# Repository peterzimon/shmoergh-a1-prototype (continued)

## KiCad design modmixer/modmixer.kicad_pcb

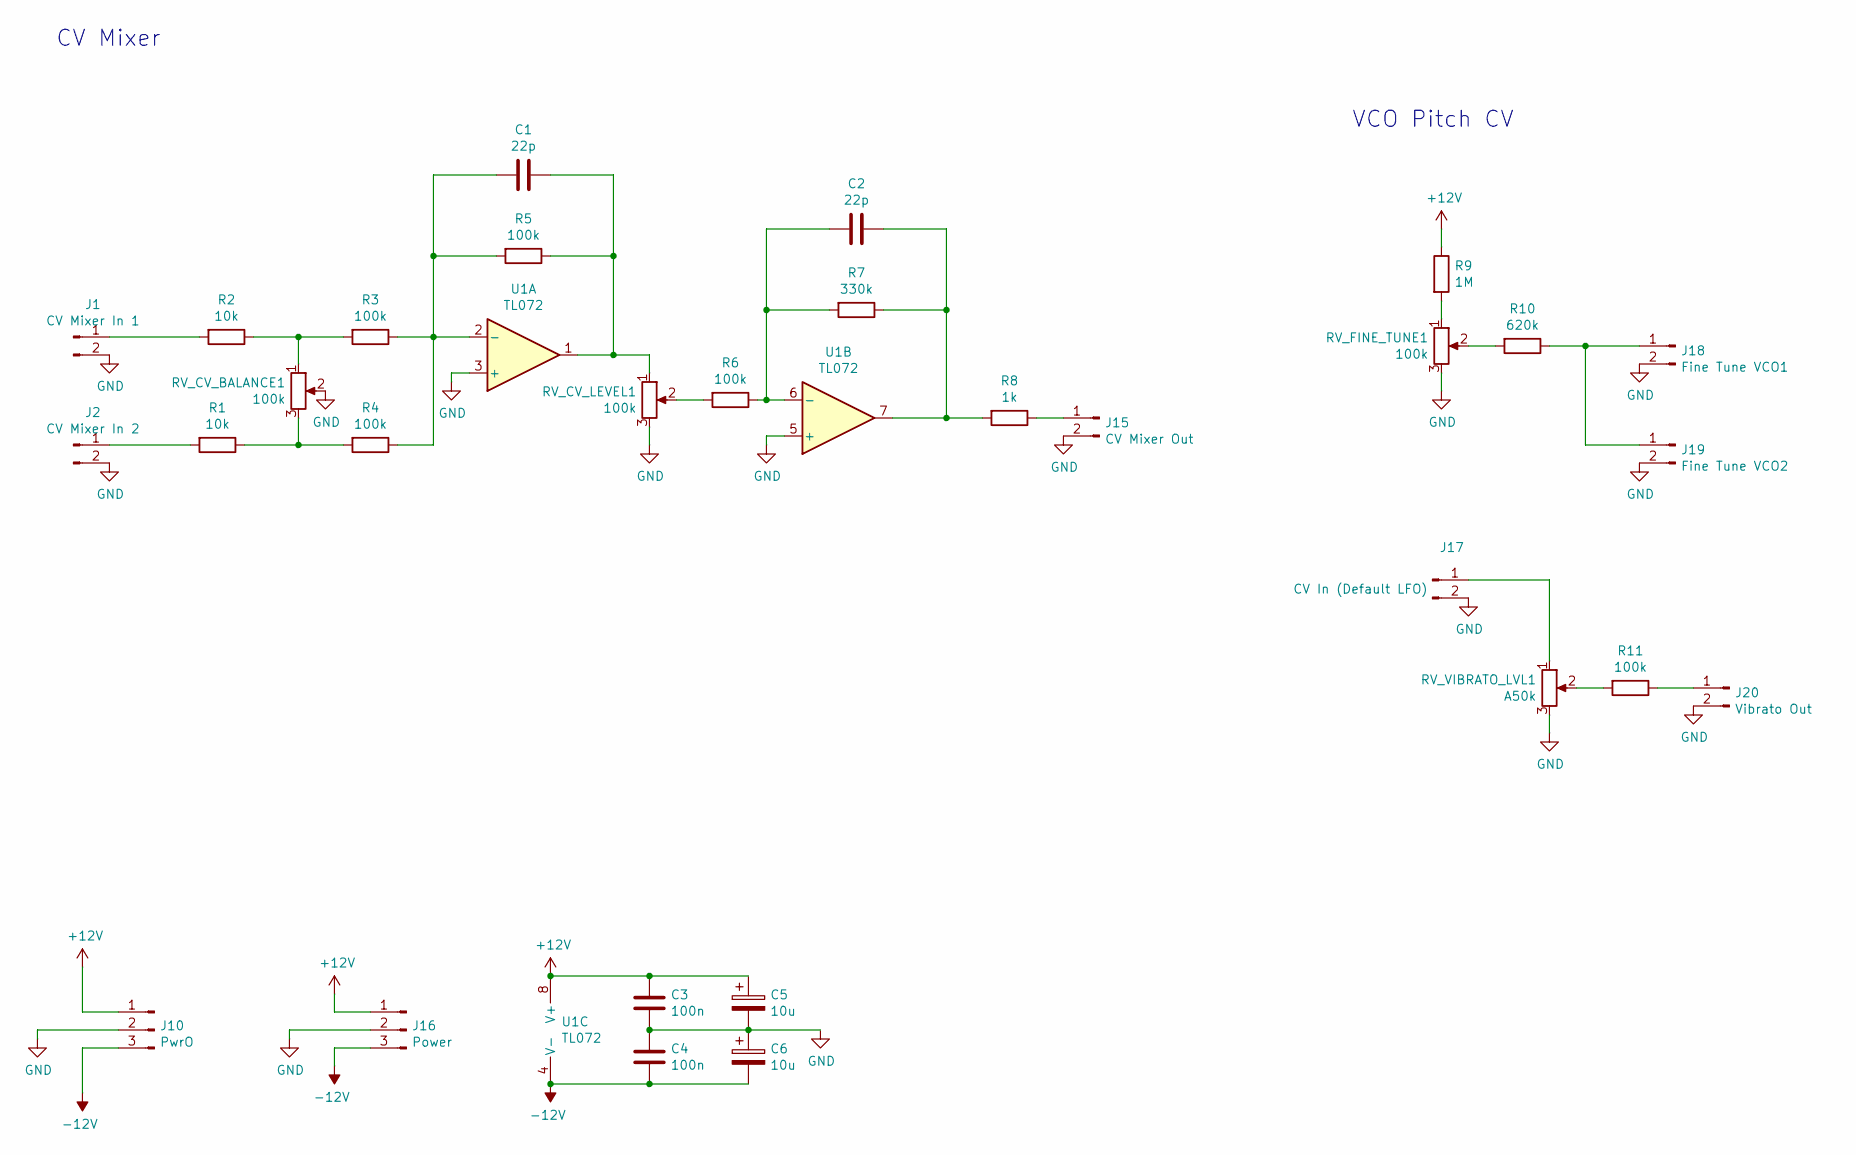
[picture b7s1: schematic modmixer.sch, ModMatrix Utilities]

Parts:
C1, C2: 22p; C_Disc_D5.0mm_W2.5mm_P2.50mm
C3, C4: 100n; C_Disc_D5.0mm_W2.5mm_P2.50mm
C5, C6: 10u; CP_Radial_D5.0mm_P2.50mm
J1: CV Mixer In 1; NSL25_01x02_Vertical
J2: CV Mixer In 2; NSL25_01x02_Vertical
J10: PwrO; NSL25_01x03_Vertical
J15: CV Mixer Out; NSL25_01x02_Vertical
J16: Power; NSL25_01x03_Vertical
J17: CV In (Default LFO); NSL25_01x02_Vertical
J18: Fine Tune VCO1; NSL25_01x02_Vertical
J19: Fine Tune VCO2; NSL25_01x02_Vertical
J20: Vibrato Out; NSL25_01x02_Vertical
R1, R2: 10k; R_Axial_Vertical
R3, R4, R5, R6, R11: 100k; R_Axial_Vertical
R7: 330k; R_Axial_Vertical
R8: 1k; R_Axial_Vertical
R9: 1M; R_Axial_Vertical
R10: 620k; R_Axial_Vertical
RV_CV_BALANCE1: 100k; NSL25_01x03_Vertical
RV_CV_LEVEL1: 100k; NSL25_01x03_Vertical
RV_FINE_TUNE1: 100k; NSL25_01x03_Vertical
RV_VIBRATO_LVL1: A50k; NSL25_01x03_Vertical
U1: TL072; DIP-8_W7.62mm

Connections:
+12V: C3.1, C5.1, J10.1, J16.1, R9.1, U1.8 (V+)
-12V: C4.2, C6.2, J10.3, J16.3, U1.4 (V-)
GND: C3.2, C4.1, C5.2, C6.1, J1.2, J2.2, J10.2, J15.2, J16.2, J17.2, J18.2, J19.2, J20.2, RV_CV_BALANCE1.2, RV_CV_LEVEL1.3, RV_FINE_TUNE1.3, RV_VIBRATO_LVL1.3, U1.3 (+), U1.5 (+)
unnamed: C1.1, R5.1, RV_CV_LEVEL1.1, U1.1
unnamed: C1.2, R3.1, R4.1, R5.2, U1.2 (-)
unnamed: C2.1, R7.1, R8.2, U1.7
unnamed: C2.2, R6.1, R7.2, U1.6 (-)
unnamed: J1.1, R2.2
unnamed: J2.1, R1.2
unnamed: J15.1, R8.1
unnamed: J17.1, RV_VIBRATO_LVL1.1
unnamed: J18.1, J19.1, R10.1
unnamed: J20.1, R11.1
unnamed: R1.1, R4.2, RV_CV_BALANCE1.3
unnamed: R2.1, R3.2, RV_CV_BALANCE1.1
unnamed: R6.2, RV_CV_LEVEL1.2
unnamed: R9.2, RV_FINE_TUNE1.1
unnamed: R10.2, RV_FINE_TUNE1.2
unnamed: R11.2, RV_VIBRATO_LVL1.2

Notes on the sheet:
CV Mixer
VCO Pitch CV

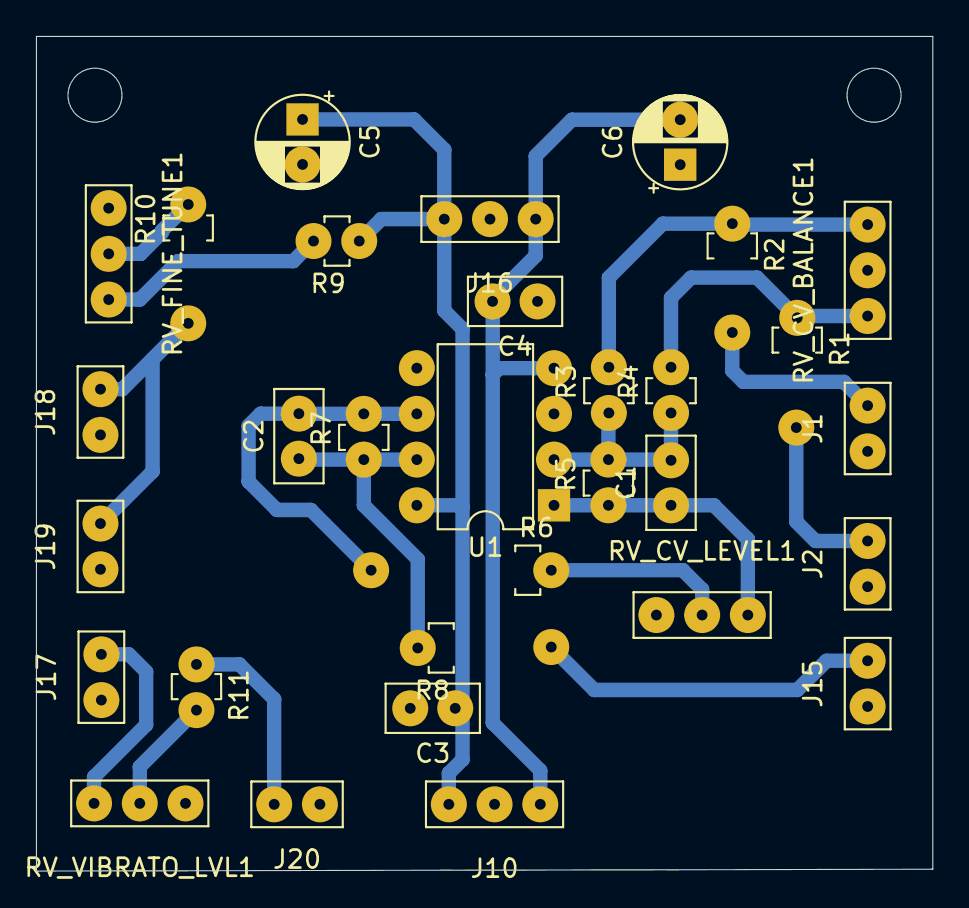
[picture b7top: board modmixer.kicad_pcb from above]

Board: 2 copper layers, 49.8 x 46.4 mm, 31 parts (0 on the bottom side), 19 nets.

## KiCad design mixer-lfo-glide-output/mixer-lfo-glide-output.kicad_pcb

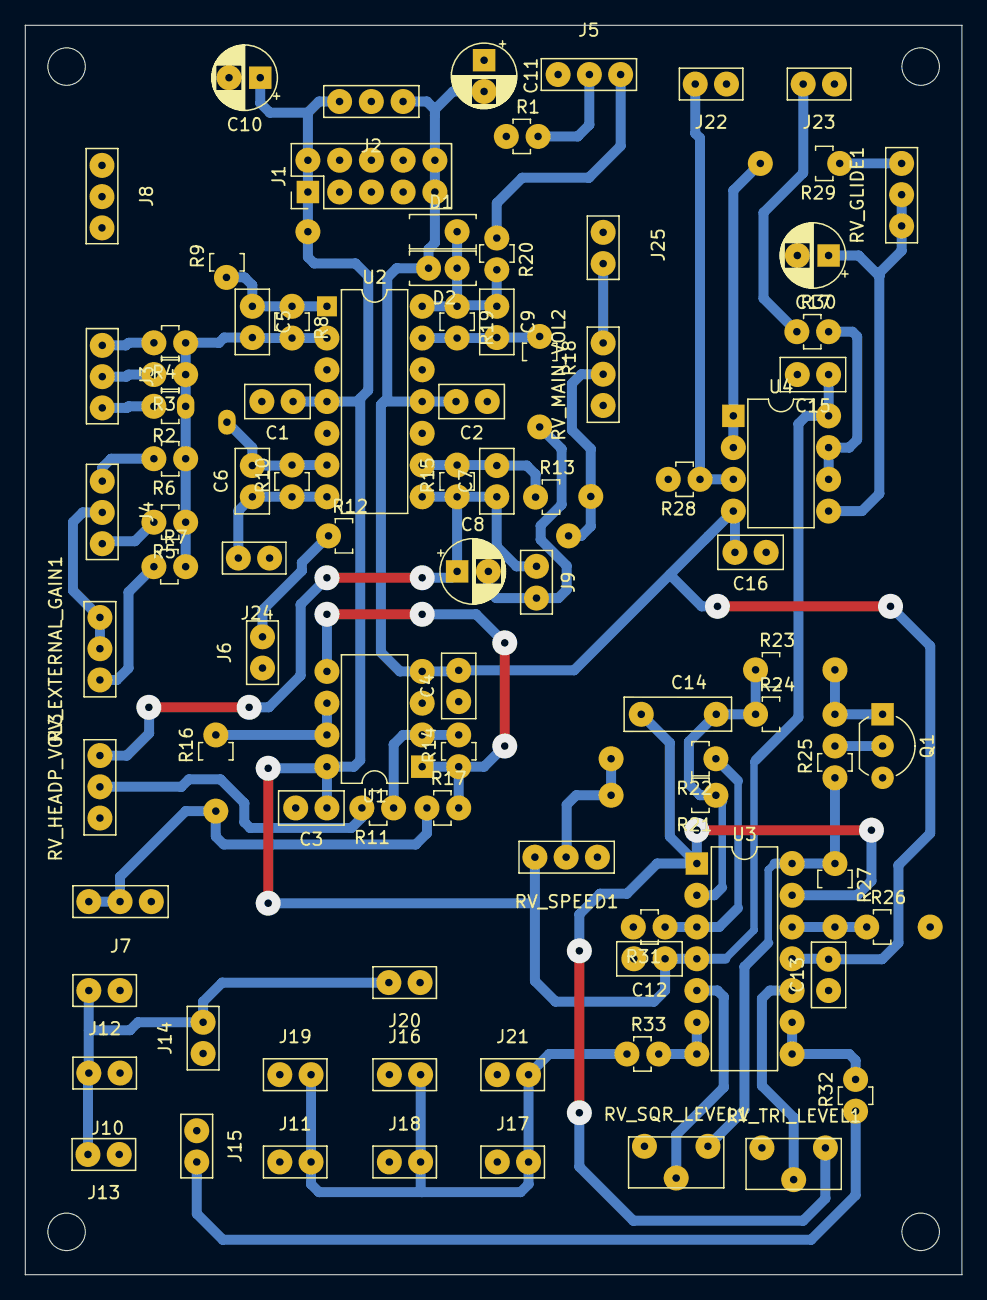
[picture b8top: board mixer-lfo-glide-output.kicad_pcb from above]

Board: 2 copper layers, 74.9 x 99.9 mm, 89 parts (0 on the bottom side), 50 nets.

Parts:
C1, C2, C3, C4, C12, C13, C15, C16: 100n; C_Disc_D5.0mm_W2.5mm_P2.50mm
C5, C6: 47p; C_Disc_D5.0mm_W2.5mm_P2.50mm
C7, C9: 22p; C_Disc_D5.0mm_W2.5mm_P2.50mm
C8, C10, C11: 10u; CP_Radial_D5.0mm_P2.50mm
C14: 100n; C_Foil_P2.50mm
C17: 1u; CP_Radial_D5.0mm_P2.50mm
D1, D2: 1N4148; D_Axial-Vertical
J1: Eurorack Power; Eurorack_Power_Supply
J2: Custom Power; NSL25_01x03_Vertical
J3: Inputs 1-3; JT_A25_01x03_Vertical
J4: Inputs 4-6; JT_A25_01x03_Vertical
J5: Line out; JT_A25_01x03_Vertical
J6: Eurorack out (10Vpp); JT_A25_01x02_Vertical
J7: Phones; JT_A25_01x03_Vertical
J8: Grounds; JT_A25_01x03_Vertical
J9: Cap Bypass Jumper; PinOut_01x02
J10: Tri From VCA; JT_A25_01x02_Vertical
J11, J16, J17, J18, J19, J21: LFO Square (5Vpp); JT_A25_01x02_Vertical
J12, J13, J14, J20: LFO Triangle (VCA); JT_A25_01x02_Vertical
J15: LFO Triangle (5Vpp); JT_A25_01x02_Vertical
J22: Glide In; JT_A25_01x02_Vertical
J23: Glide Out; JT_A25_01x02_Vertical
J24: 10Vpp to VCA; JT_A25_01x02_Vertical
J25: From 10Vpp VCA; JT_A25_01x02_Vertical
Q1: BC548; TO-92_Inline_Wide
R1, R12, R20, R30, R32, R33: 1k; R_Axial_Vertical
R2, R3, R4, R5, R6, R8, R9, R10, R13, R21, R22, R23, R24, R28, R31: 100k; R_Axial_Vertical
R7, R11, R14, R18, R19, R25: 10k; R_Axial_Vertical
R15: 33k; R_Axial_Vertical
R16, R17, R29: 100; R_Axial_Vertical
R26, R27: 47k; R_Axial_Vertical
RV_EXTERNAL_GAIN1: 100k; JT_A25_01x03_Vertical
RV_GLIDE1: A500k; JT_A25_01x03_Vertical
RV_HEADP_VOL3: A50k; JT_A25_01x03_Vertical
RV_MAIN_VOL2: A50k; JT_A25_01x03_Vertical
RV_SPEED1: 10k; JT_A25_01x03_Vertical
RV_SQR_LEVEL1: 10k; TrimPot_Vertical
RV_TRI_LEVEL1: 10k; TrimPot_Vertical
U1: NE5532; DIP-8_W7.62mm
U2, U3: TL074; DIP-14_W7.62mm
U4: TL072; DIP-8_W7.62mm

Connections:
+12V: C1.1, C3.1, C10.1, C12.1, C15.1, D1.1, J1.1, J1.2, J2.1, RV_SPEED1.1, U1.8, U2.4, U3.4, U4.8
-12V: C2.2, C4.2, C11.2, C13.2, C16.2, D2.2, J1.9, J1.10, J2.3, U1.4, U2.11, U3.11, U4.4
EURO_OUT: J6.1, R12.1
FROM_VOICE_VCA: J25.1, RV_MAIN_VOL2.1
GND: C1.2, C2.1, C3.2, C4.1, C10.2, C11.1, C12.2, C13.1, C15.2, C16.1, C17.2, J1.3, J1.4, J1.5, J1.6, J1.7, J1.8, J2.2, J5.3, J6.2, J7.3, J8.1, J8.2, J8.3, J10.2, J11.2, J12.2, J13.2, J14.2, J15.2, J16.2, J17.2, J18.2, J19.2, J20.2, J21.2, J22.2, J23.2, J24.2, J25.2, Q1.3, R1.1, R26.2, R28.2, R31.2, RV_HEADP_VOL3.3, RV_MAIN_VOL2.3, RV_SPEED1.3, RV_SQR_LEVEL1.3, RV_TRI_LEVEL1.3, U1.3, U2.3, U2.5, U2.10, U2.12
IN_EXTERNAL: J4.2, RV_EXTERNAL_GAIN1.1, RV_EXTERNAL_GAIN1.2
IN_EXTRA: J4.3, R6.2
IN_NOISE: J4.1, R5.2
IN_SUB: J3.3, R4.2
IN_VCO1: J3.1, R2.2
IN_VCO2: J3.2, R3.2
LFO_SQR_OUT: J11.1, J16.1, J17.1, J18.1, J19.1, J21.1, R33.1
LFO_TRI_OUT: J10.1, J12.1, J13.1, J14.1, J20.1
LINE_OUT: J5.1, R20.1
unnamed: C5.1, R8.1, R9.2, U2.1
unnamed: C5.2, R2.1, R3.1, R4.1, R5.1, R6.1, R7.2, R8.2, U2.2
unnamed: C6.2, R9.1, R10.2, U2.6
unnamed: C7.1, C8.1, J9.2, R15.1, RV_HEADP_VOL3.1, U2.8
unnamed: C7.2, R13.1, R15.2, U2.9
unnamed: C8.2, J9.1, R18.2
unnamed: C9.1, D1.2, D2.1, R19.1, R20.2, U2.14
unnamed: C9.2, R18.1, R19.2, U2.13
unnamed: C14.1, RV_TRI_LEVEL1.1, U3.1, U3.13
unnamed: C14.2, R21.1, R23.1, R24.1, U3.2
unnamed: C17.1, RV_GLIDE1.2, RV_GLIDE1.3, U4.5
unnamed: J5.2, R1.2
unnamed: Q1.1, R23.2, R24.2
unnamed: Q1.2, R25.2
unnamed: R7.1, RV_EXTERNAL_GAIN1.3
unnamed: R11.1, R14.2, U1.2
unnamed: R11.2, RV_HEADP_VOL3.2
unnamed: R12.2, R13.2, RV_MAIN_VOL2.2
unnamed: R14.1, R17.2, U1.1, U1.5
unnamed: R16.2, U1.6, U1.7
unnamed: R21.2, R22.2, RV_SPEED1.2
unnamed: R22.1, R31.1, U3.3
unnamed: R25.1, R27.1, RV_SQR_LEVEL1.1, U3.14
unnamed: R26.1, R27.2, U3.12
unnamed: R29.1, RV_GLIDE1.1
unnamed: R29.2, U4.1, U4.2
unnamed: R30.2, U4.6, U4.7
unnamed: R32.2, U3.8, U3.9
unnamed: R33.2, U3.6, U3.7
unnamed: RV_SQR_LEVEL1.2, U3.5
unnamed: RV_TRI_LEVEL1.2, U3.10
PHONES_OUT: J7.1, J7.2, R16.1, R17.1
PITCH_IN: J22.1, R28.1, U4.3
PITCH_OUT: J23.1, R30.1
TO_VOICE_VCA: C6.1, J24.1, R10.1, U2.7
TRI_TO_VCA: J15.1, R32.1

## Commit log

2022-01-15 Cleanup
2022-01-15 Updated VCO plots
